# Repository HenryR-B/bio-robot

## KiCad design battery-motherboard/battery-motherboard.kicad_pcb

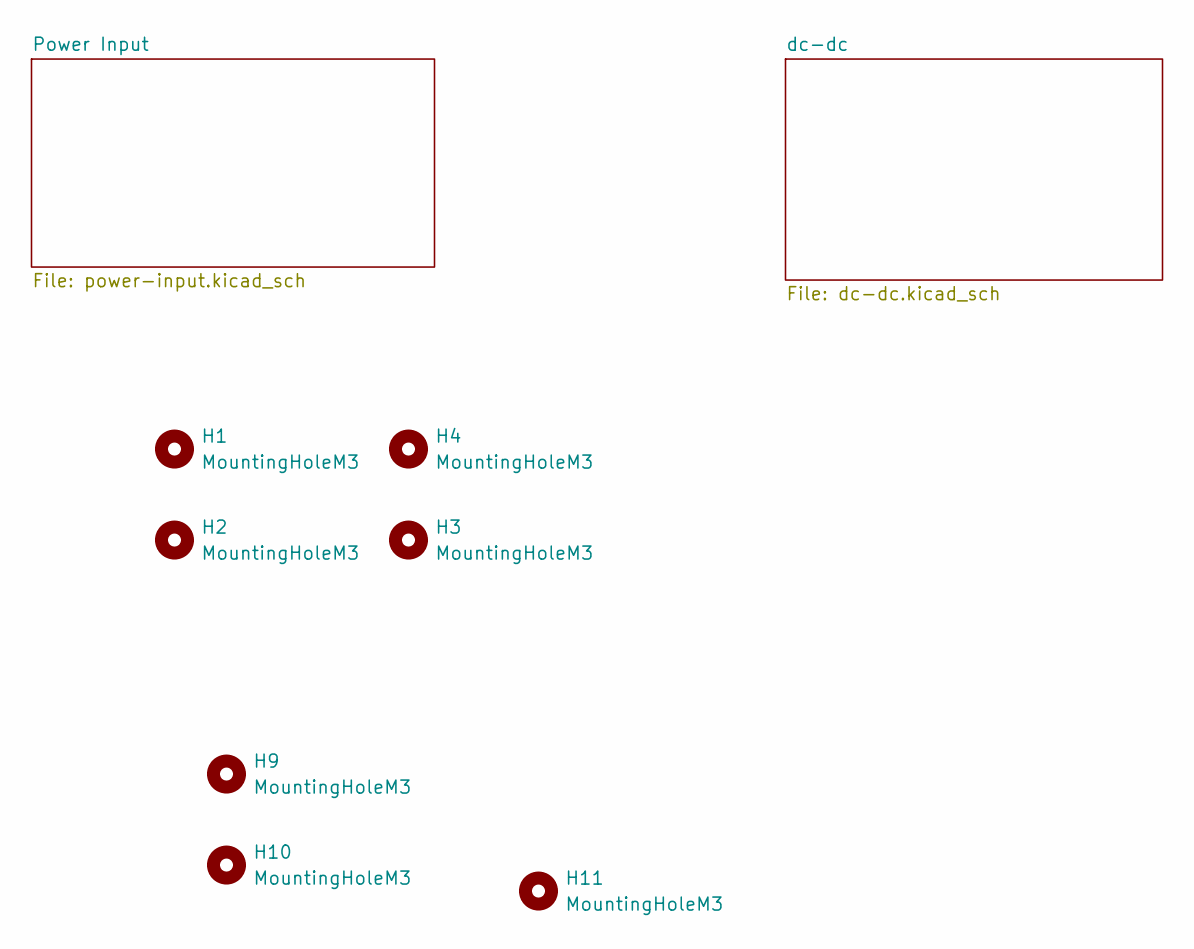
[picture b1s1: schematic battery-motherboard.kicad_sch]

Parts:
H1, H2, H3, H4, H9, H10, H11: MountingHoleM3; MountingHole_3.2mm_M3_DIN965_Pad

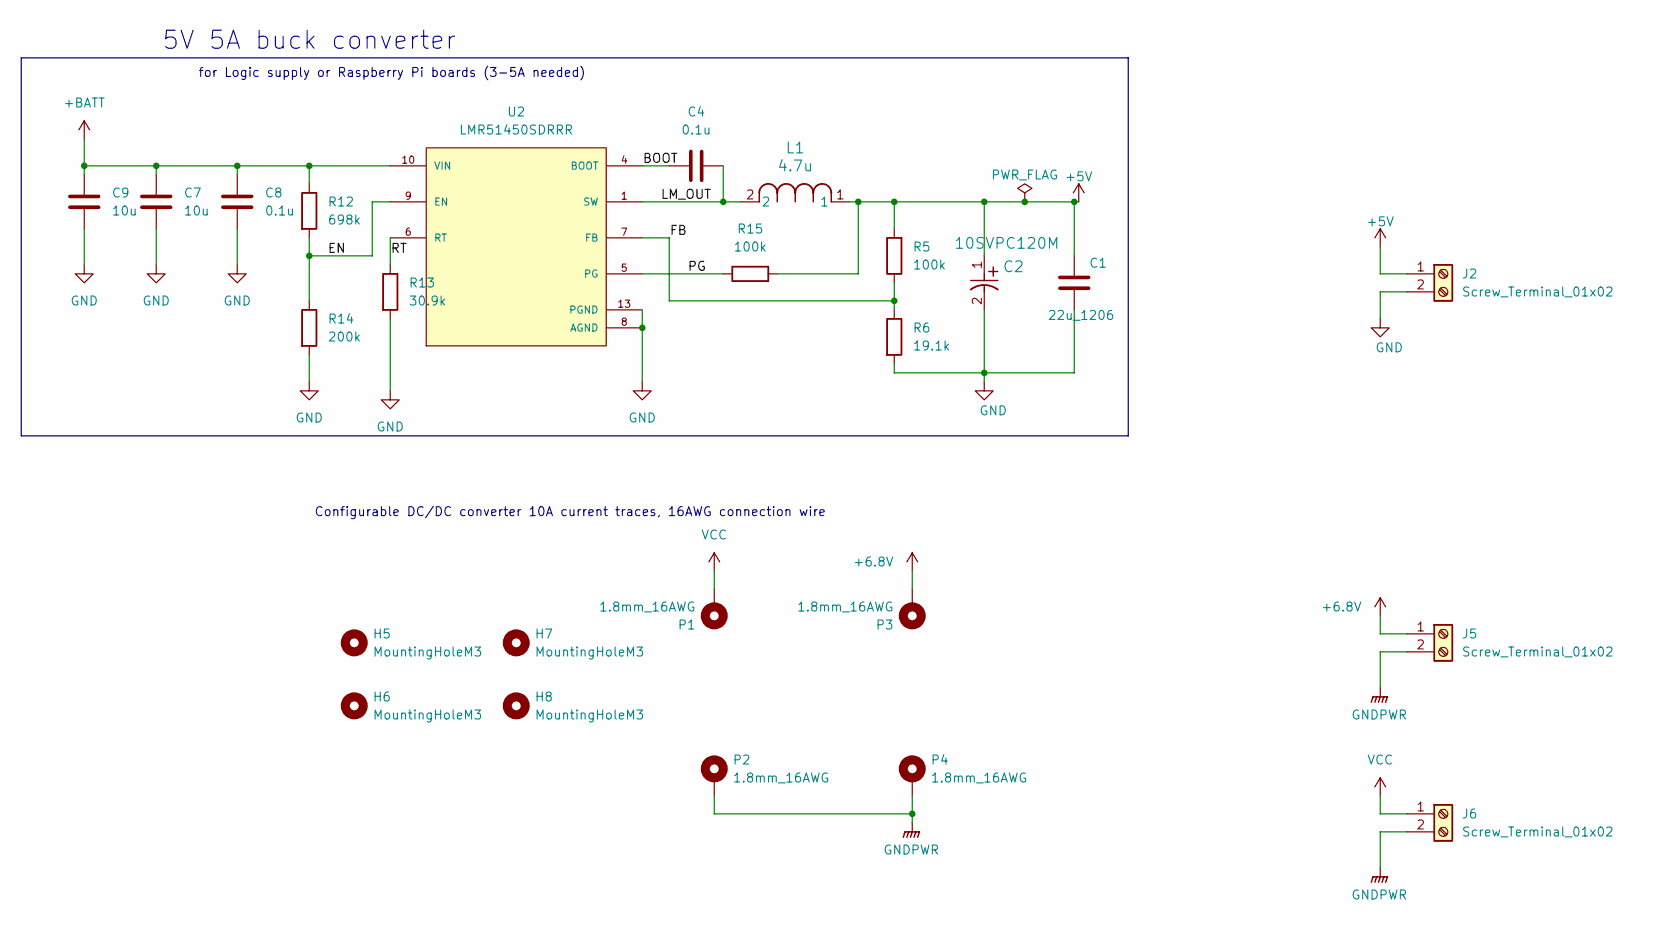
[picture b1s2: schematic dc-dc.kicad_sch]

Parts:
C1: 22u_1206; C_1206_3216Metric; MPN CL31A226KAHNNNE; JLC 0805
C2: 10SVPC120M; CAP_10SVPC120MV; LCSC C178336
C4, C8: 0.1u; C_0603_1608Metric; MPN CC0603KRX7R9BB104; JLC 0603
C7, C9: 10u; C_0805_2012Metric; MPN GRM21BR61H106KE43L; JLC 0805
H5, H6, H7, H8: MountingHoleM3; MountingHole_3.2mm_M3_DIN965_Pad
J2, J5, J6: Screw_Terminal_01x02; TerminalBlock_MaiXu_MX126-5.0-02P_1x02_P5.00mm
L1: 4.7u; IND_XAL6060-472MEC; MPN XAL6060-472MEB; LCSC C7421717
P1, P2, P3, P4: 1.8mm_16AWG; SolderPad_TH_16AWG_1.8mm
R5, R15: 100k; R_0603_1608Metric; MPN 0603WAF1003T5E; JLC 0603
R6: 19.1k; R_0603_1608Metric; MPN 0603WAF1912T5E; JLC 0603
R12: 698k; R_0603_1608Metric; MPN 0603WAF6983T5E; JLC 0603
R13: 30.9k; R_0603_1608Metric; MPN 0603WAF3092T5E; JLC 0603
R14: 200k; R_0603_1608Metric; MPN 0603WAF2003T5E; JLC 0603
U2: LMR51450SDRRR; CONV_LMR51450SDRRR; PARTREV December 2022

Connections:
+5V: C1.1, C2.1, J2.1, L1.1, R5.2, R15.2; also elsewhere on the board
+6.8V: J5.1, P3.1 (1_1); also elsewhere on the board
+BATT: C7.1, C8.2, C9.1, R12.1, U2.10 (VIN), U2.11 (VIN), U2.12 (VIN); also elsewhere on the board
/dc-dc/BOOT: C4.1, U2.4 (BOOT)
/dc-dc/EN: R12.2, R14.1, U2.9 (EN)
/dc-dc/FB: R5.1, R6.1, U2.7 (FB)
/dc-dc/LM_OUT: C4.2, L1.2, U2.1 (SW), U2.2 (SW), U2.3 (SW)
/dc-dc/PG: R15.1, U2.5 (PG)
/dc-dc/RT: R13.1, U2.6 (RT)
GND: C1.2, C2.2, C7.2, C8.1, C9.2, J2.2, R6.2, R13.2, R14.2, U2.8 (AGND), U2.13 (PGND); also elsewhere on the board
GNDPWR: J5.2, J6.2, P2.1 (1_1), P4.1 (1_1); also elsewhere on the board
VCC: J6.1, P1.1 (1_1); also elsewhere on the board

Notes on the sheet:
Configurable DC/DC converter 10A current traces, 16AWG connection wire
5V 5A buck converter
for Logic supply or Raspberry Pi boards (3-5A needed)

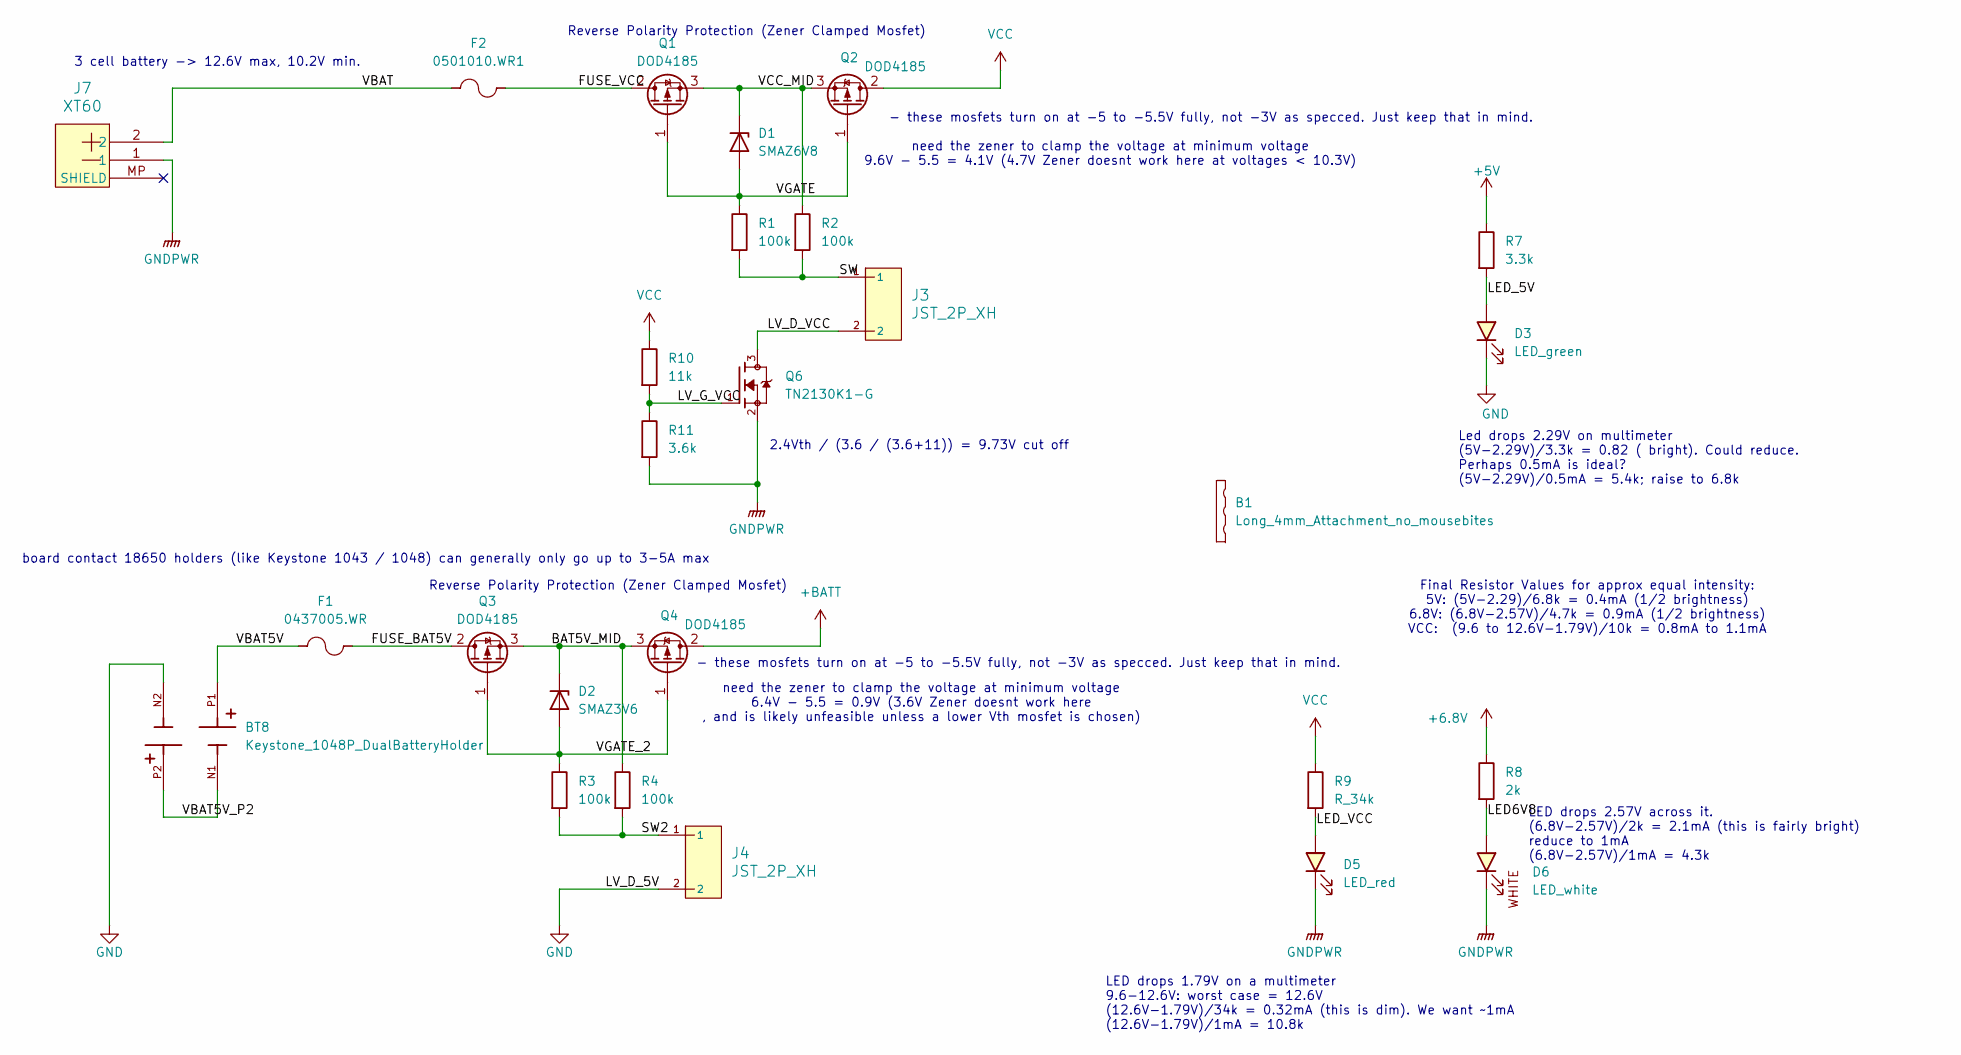
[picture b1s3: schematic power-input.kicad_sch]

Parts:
B1: Long_4mm_Attachment_no_mousebites; Long_4mm_attachment_no_mouse_bites
BT8: Keystone_1048P_DualBatteryHolder; BAT_1048P; PARTREV E; DigiKey_Part_Number 36-1042-ND
D1: SMAZ6V8; D_SMA; MPN SMAZ6V8; JLC DO-214AC(SMA)
D2: SMAZ3V6; D_SMA; MPN 1SMA4729A; LCSC C19077475
D3: LED_green; LED_0805_2012Metric; MPN KT-0805G; JLC 0805
D5: LED_red; LED_0805_2012Metric; MPN NCD0805R1; JLC 0805
D6: LED_white; LED_0603_1608Metric; MPN KT-0603W; JLC 0603
F1: 0437005.WR; Fuse_1206_3216Metric; MPN 0501010.WR1; JLC 1206
F2: 0501010.WR1; Fuse_1206_3216Metric; MPN 0501010.WR1; JLC 1206
J3, J4: JST_2P_XH; JST_B2B-XH-A_LF__SN_
J7: XT60; AMASS_XT60PW-M
Q1, Q2, Q3, Q4: DOD4185; DPAK-3_ONS; MPN DOD4185; LCSC C41430591
Q6: TN2130K1-G; SOT95P240X111-3N; MPN TN2130K1-G; JLC SOT-23-3
R1, R2, R3, R4: 100k; R_0603_1608Metric; MPN 0603WAF1003T5E; JLC 0603
R7: 3.3k; R_0603_1608Metric; MPN 0603WAF3301T5E; JLC 0603
R8: 2k; R_0603_1608Metric; MPN 0603WAF2001T5E; JLC 0603
R9: R_34k; R_0603_1608Metric; MPN 0603WAF3402T5E; JLC 0603
R10: 11k; R_0603_1608Metric; MPN 0603WAF1102T5E; JLC 0603
R11: 3.6k; R_0603_1608Metric; MPN 0603WAF3601T5E; JLC 0603

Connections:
+5V: R7.1; also elsewhere on the board
+6.8V: R8.1; also elsewhere on the board
+BATT: Q4.2 (D); also elsewhere on the board
/Power Input/BAT5V_MID: D2.1 (K), Q3.3 (S), Q4.3 (S), R4.1
/Power Input/FUSE_BAT5V: F1.2, Q3.2 (D)
/Power Input/FUSE_VCC: F2.2, Q1.2 (D)
/Power Input/LED6V8: D6.2 (A), R8.2
/Power Input/LED_5V: D3.2 (A), R7.2
/Power Input/LED_VCC: D5.2 (A), R9.2
/Power Input/LV_D_VCC: J3.2, Q6.3
/Power Input/LV_G_VCC: Q6.1, R10.2, R11.1
/Power Input/SW: J3.1, R1.2, R2.2
/Power Input/SW2: J4.1, R3.2, R4.2
/Power Input/VBAT: F2.1, J7.2
/Power Input/VBAT5V: BT8.P1, F1.1
/Power Input/VBAT5V_P2: BT8.N1, BT8.P2
/Power Input/VCC_MID: D1.1 (K), Q1.3 (S), Q2.3 (S), R2.1
/Power Input/VGATE: D1.2 (A), Q1.1 (G), Q2.1 (G), R1.1
/Power Input/VGATE_2: D2.2 (A), Q3.1 (G), Q4.1 (G), R3.1
GND: BT8.N2, D3.1 (K), J4.2; also elsewhere on the board
GNDPWR: D5.1 (K), D6.1 (K), J7.1, Q6.2, R11.2; also elsewhere on the board
VCC: Q2.2 (D), R9.1, R10.1; also elsewhere on the board

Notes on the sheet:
3 cell battery -> 12.6V max, 10.2V min.
Reverse Polarity Protection (Zener Clamped Mosfet)
2.4Vth / (3.6 / (3.6+11)) = 9.73V cut off
board contact 18650 holders (like Keystone 1043 / 1048) can generally only go up to 3-5A max
LED drops 2.57V across it. (6.8V-2.57V)/2k = 2.1mA (this is fairly bright) reduce to 1mA (6.8V-2.57V)/1mA = 4.3k
Final Resistor Values for approx equal intensity: 5V: (5V-2.29)/6.8k = 0.4mA (1/2 brightness) 6.8V: (6.8V-2.57V)/4.7k = 0.9mA (1/2 brightness) VCC: (9.6 to 12.6V-1.79V)/10k = 0.8mA to 1.1mA
need the zener to clamp the voltage at minimum voltage 9.6V - 5.5 = 4.1V (4.7V Zener doesnt work here at voltages < 10.3V)
- these mosfets turn on at -5 to -5.5V fully, not -3V as specced. Just keep that in mind.
need the zener to clamp the voltage at minimum voltage 6.4V - 5.5 = 0.9V (3.6V Zener doesnt work here , and is likely unfeasible unless a lower Vth mosfet is chosen)
LED drops 1.79V on a multimeter 9.6-12.6V: worst case = 12.6V (12.6V-1.79V)/34k = 0.32mA (this is dim). We want ~1mA (12.6V-1.79V)/1mA = 10.8k
Led drops 2.29V on multimeter (5V-2.29V)/3.3k = 0.82 ( bright). Could reduce. Perhaps 0.5mA is ideal? (5V-2.29V)/0.5mA = 5.4k; raise to 6.8k

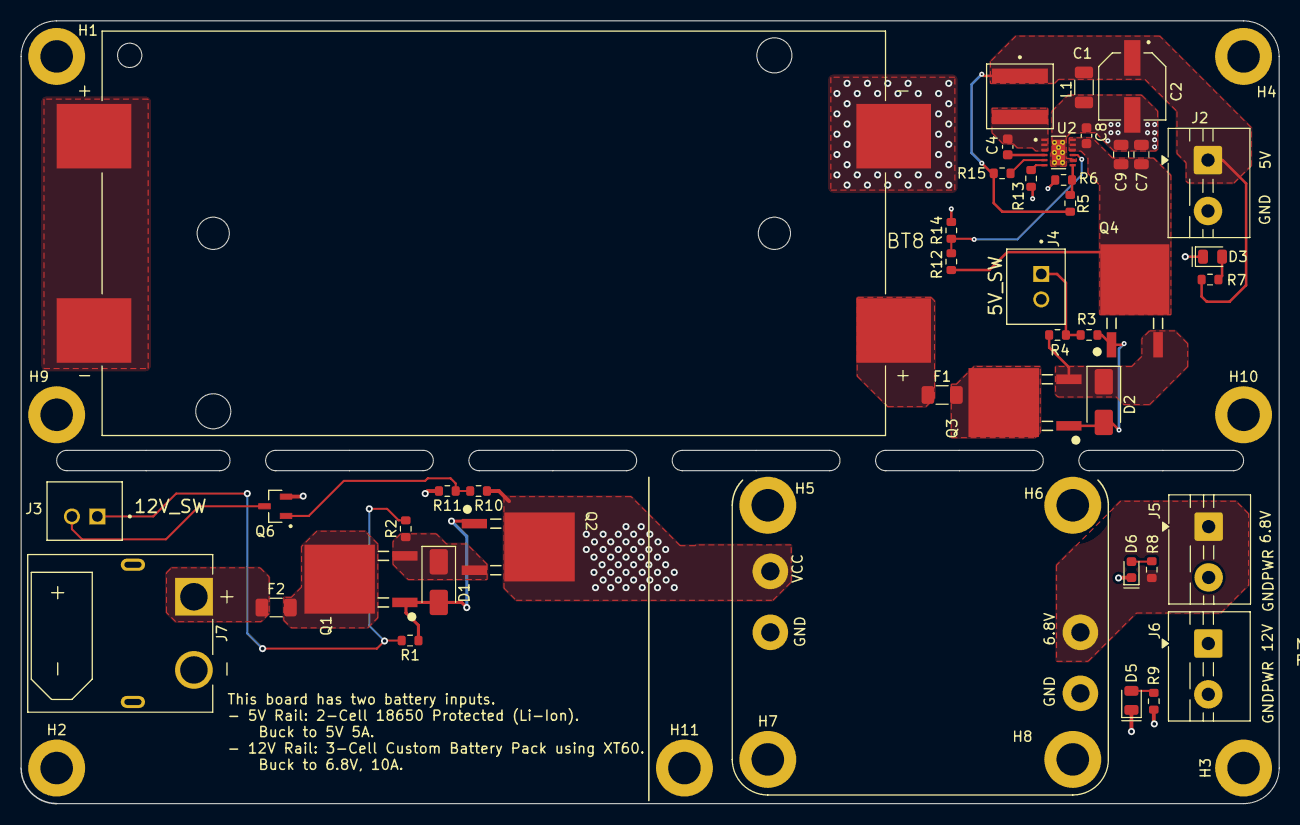
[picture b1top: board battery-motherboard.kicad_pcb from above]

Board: 4 copper layers, 123.7 x 77.0 mm, 58 parts (0 on the bottom side), 28 nets.

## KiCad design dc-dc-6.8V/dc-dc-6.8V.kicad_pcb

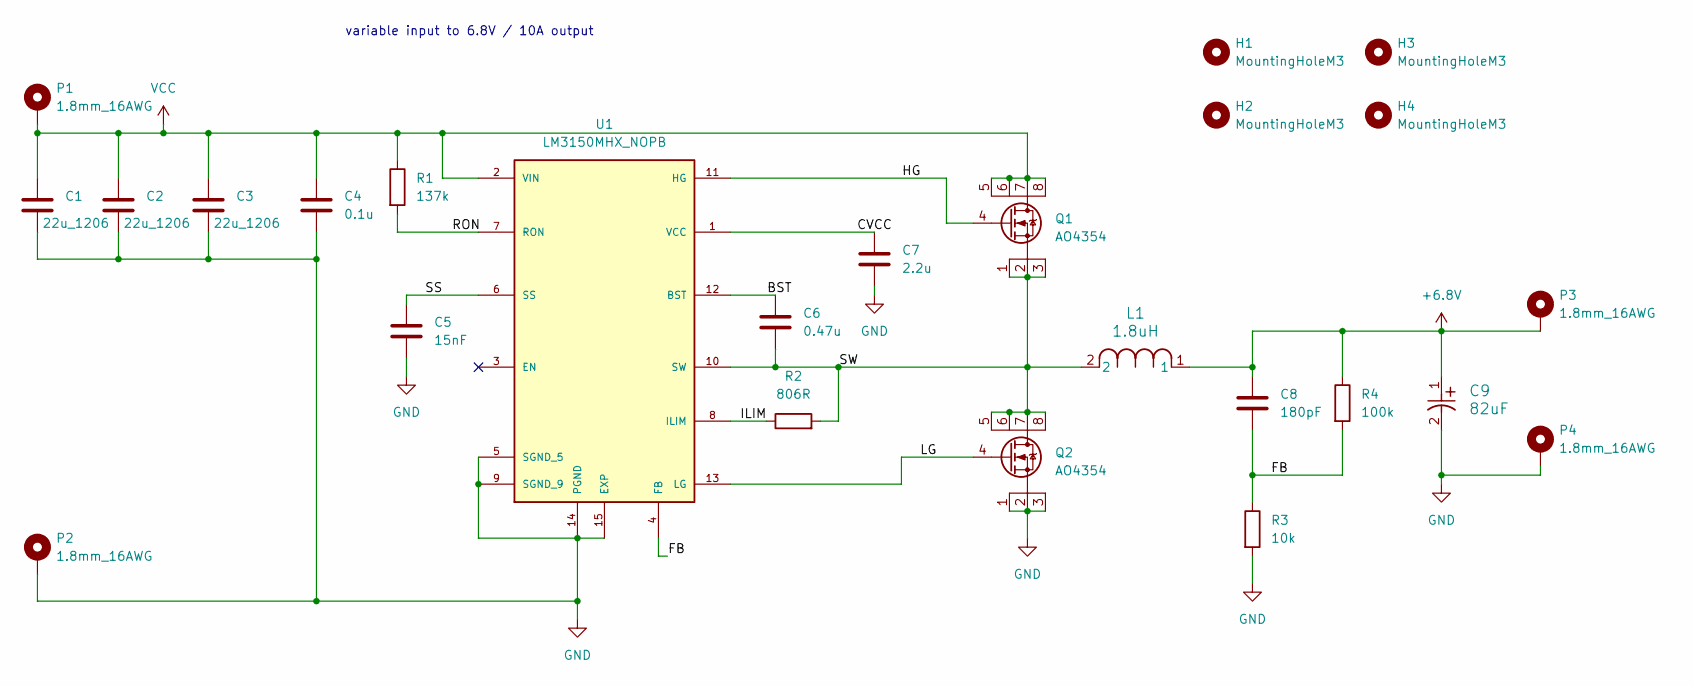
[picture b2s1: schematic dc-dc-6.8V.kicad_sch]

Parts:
C1, C2, C3: 22u_1206; C_1206_3216Metric; MPN CL31A226KAHNNNE; JLC 0805
C4: 0.1u; C_0603_1608Metric; MPN CC0603KRX7R9BB104; JLC 0603
C5: 15nF; C_0603_1608Metric; MPN 0603B153K500NT; JLC 0603
C6: 0.47u; C_0603_1608Metric; MPN CL10B474KA8NNNC; JLC 0603
C7: 2.2u; C_0603_1608Metric; MPN CL10A225KO8NNNC; JLC 0603
C8: 180pF; C_0603_1608Metric; MPN CL10C181JB8NNNC; JLC 0603
C9: 82uF; CAP_10SVPC120MV; MPN 10SVPC120MV; LCSC C178336
H1, H2, H3, H4: MountingHoleM3; MountingHole_3.2mm_M3_DIN965_Pad
L1: 1.8uH; IND_XAL7070_COC; MPN XAL7070-182MEC; LCSC C3911679
P1, P2, P3, P4: 1.8mm_16AWG; SolderPad_TH_16AWG_1.8mm
Q1, Q2: AO4354; SOIC-8_3.9x4.9mm_P1.27mm; MPN AO4354; LCSC C61955
R1: 137k; R_0603_1608Metric; MPN 0603WAF1373T5E; JLC 0603
R2: 806R; R_0603_1608Metric; MPN 0603WAF8060T5E; JLC 0603
R3: 10k; R_0603_1608Metric; MPN 0603WAF1002T5E; JLC 0603
R4: 100k; R_0603_1608Metric; MPN 0603WAF1003T5E; JLC 0603
U1: LM3150MHX_NOPB; SOP65P640X110-15N; PARTREV G

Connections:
+6.8V: C8.1, C9.1, L1.1, P3.1 (1_1), R4.1
/BST: C6.1, U1.12 (BST)
/CVCC: C7.1, U1.1 (VCC)
/FB: C8.2, R3.1, R4.2, U1.4 (FB)
/HG: Q1.4 (G), U1.11 (HG)
/ILIM: R2.1, U1.8 (ILIM)
/LG: Q2.4 (G), U1.13 (LG)
/RON: R1.2, U1.7 (RON)
/SS: C5.1, U1.6 (SS)
/SW: C6.2, L1.2, Q1.1 (S), Q1.2 (S), Q1.3 (S), Q2.5 (D), Q2.6 (D), Q2.7 (D), Q2.8 (D), R2.2, U1.10 (SW)
GND: C1.2, C2.2, C3.2, C4.2, C5.2, C7.2, C9.2, P2.1 (1_1), P4.1 (1_1), Q2.1 (S), Q2.2 (S), Q2.3 (S), R3.2, U1.5 (SGND_5), U1.9 (SGND_9), U1.14 (PGND), U1.15 (EXP)
VCC: C1.1, C2.1, C3.1, C4.1, P1.1 (1_1), Q1.5 (D), Q1.6 (D), Q1.7 (D), Q1.8 (D), R1.1, U1.2 (VIN)

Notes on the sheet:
variable input to 6.8V / 10A output

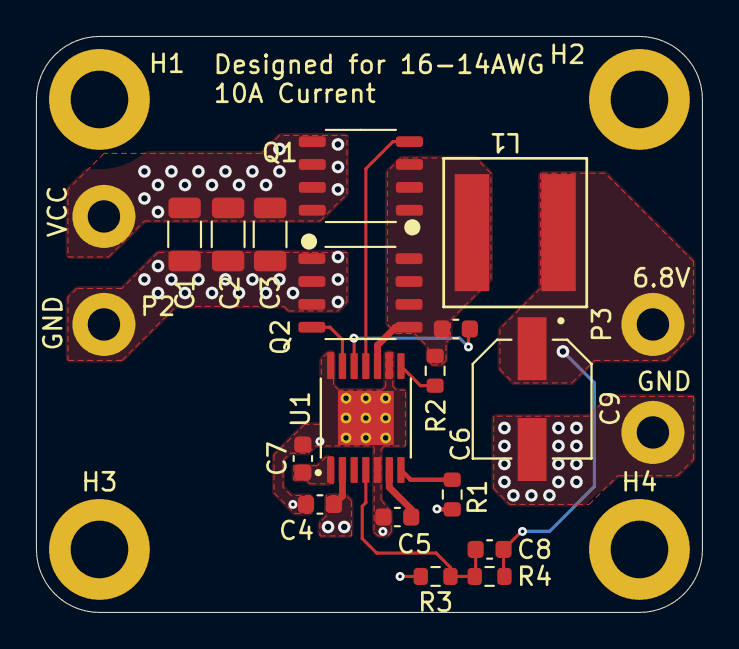
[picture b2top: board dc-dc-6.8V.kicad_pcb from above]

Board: 4 copper layers, 37.0 x 32.0 mm, 25 parts (0 on the bottom side), 12 nets.

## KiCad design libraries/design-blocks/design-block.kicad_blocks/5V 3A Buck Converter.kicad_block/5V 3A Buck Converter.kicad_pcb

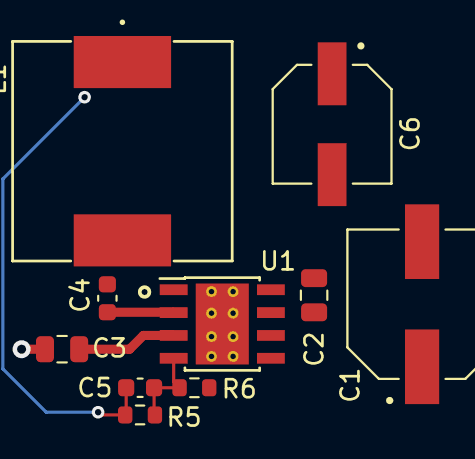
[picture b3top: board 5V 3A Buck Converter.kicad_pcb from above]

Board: 4 copper layers, 10 parts (0 on the bottom side), 7 nets.

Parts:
C1: 25SVPF100M; CAP_25SVPF100M
C2: 10u; C_0805_2012Metric
C3: 2.2u; C_0805_2012Metric
C4: 0.1u; C_0603_1608Metric
C5: 30p; C_0603_1608Metric
C6: 16SVPF180M; CAP_16SVPF180M
L1: 27uH; IND_CDRH127_LDNP-470MC_SUM
R5: 88.7k; R_0603_1608Metric
R6: 22.1k; R_0603_1608Metric
U1: LMR23630AFDDAR; TI_SO-PowerPAD-8_ThermalVias

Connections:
+5V: C5.1, C6.1, L1.1, R5.1
+BATT: C1.1, C2.1, U1.5 (EN/SYNC), U1.7 (VIN)
/dc-dc/BOOT: C4.1, U1.2 (BOOT)
/dc-dc/FB: C5.2, R5.2, R6.1, U1.4 (FB)
/dc-dc/LM_OUT: C4.2, L1.2, U1.1 (SW)
/dc-dc/U1_VCC: C3.1, U1.3 (VCC)
GND: C1.2, C2.2, C3.2, C6.2, R6.2, U1.6 (AGND), U1.8 (PGND), U1.9 (PAD)

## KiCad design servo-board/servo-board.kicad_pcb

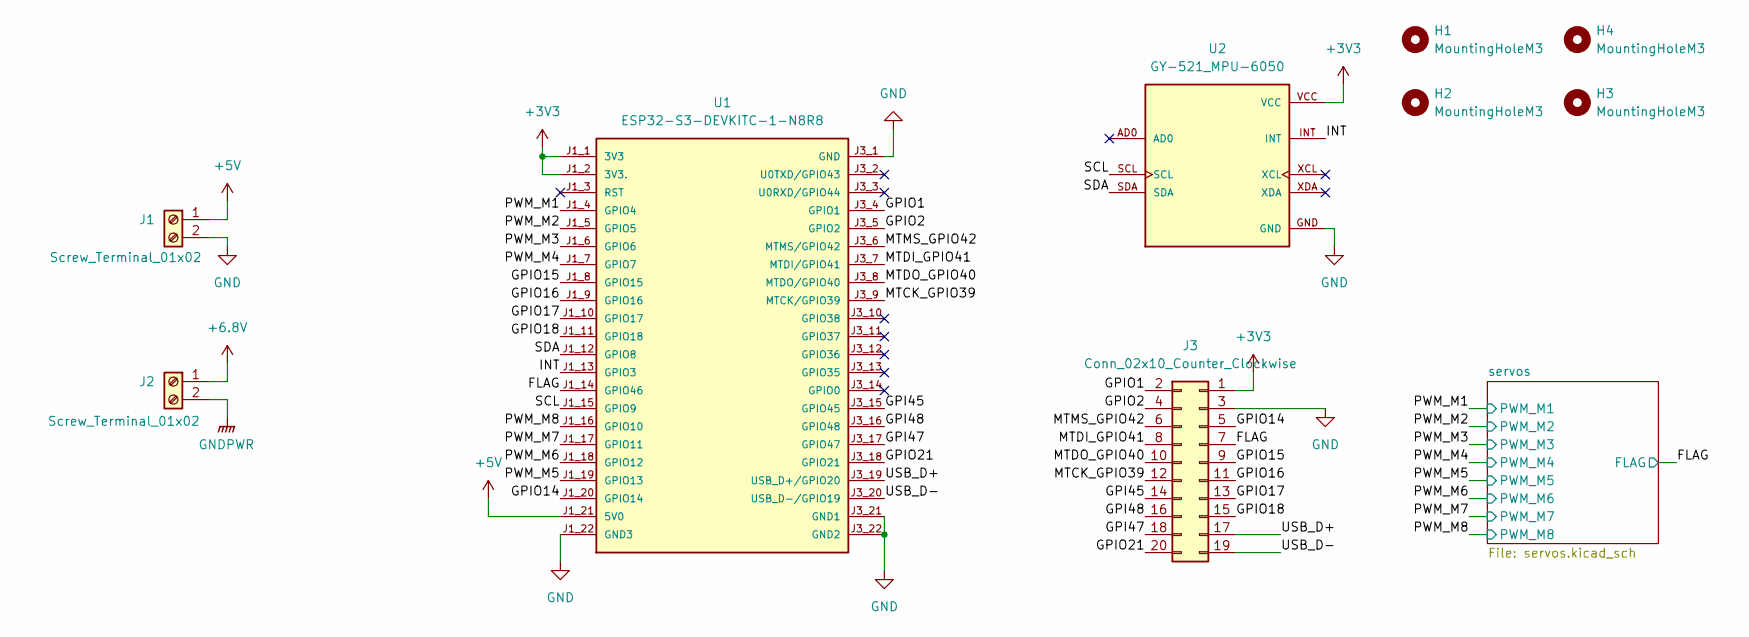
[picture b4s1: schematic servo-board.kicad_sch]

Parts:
H1, H2, H3, H4: MountingHoleM3; MountingHole_3.2mm_M3_DIN965_Pad
J1, J2: Screw_Terminal_01x02; TerminalBlock_MaiXu_MX126-5.0-02P_1x02_P5.00mm
J3: Conn_02x10_Counter_Clockwise; PinSocket_2x10_P2.54mm_Vertical
U1: ESP32-S3-DEVKITC-1-N8R8
U2: GY-521_MPU-6050; MODULE_OC09600; PARTREV NA

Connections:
+3V3: J3.1, U1.J1_1 (3V3), U1.J1_2 (3V3.), U2.VCC; also elsewhere on the board
+5V: J1.1, U1.J1_21 (5V0)
+6.8V: J2.1; also elsewhere on the board
/FLAG: J3.7, U1.J1_14 (GPIO46); also elsewhere on the board
/GPI45: J3.14, U1.J3_15 (GPIO45)
/GPI47: J3.18, U1.J3_17 (GPIO47)
/GPI48: J3.16, U1.J3_16 (GPIO48)
/GPIO1: J3.2, U1.J3_4 (GPIO1)
/GPIO2: J3.4, U1.J3_5 (GPIO2)
/GPIO14: J3.5, U1.J1_20 (GPIO14)
/GPIO15: J3.9, U1.J1_8 (GPIO15)
/GPIO16: J3.11, U1.J1_9 (GPIO16)
/GPIO17: J3.13, U1.J1_10 (GPIO17)
/GPIO18: J3.15, U1.J1_11 (GPIO18)
/GPIO21: J3.20, U1.J3_18 (GPIO21)
/INT: U1.J1_13 (GPIO3), U2.INT
/MTCK_GPIO39: J3.12, U1.J3_9 (MTCK/GPIO39)
/MTDI_GPIO41: J3.8, U1.J3_7 (MTDI/GPIO41)
/MTDO_GPIO40: J3.10, U1.J3_8 (MTDO/GPIO40)
/MTMS_GPIO42: J3.6, U1.J3_6 (MTMS/GPIO42)
/PWM_M1: U1.J1_4 (GPIO4); also elsewhere on the board
/PWM_M2: U1.J1_5 (GPIO5); also elsewhere on the board
/PWM_M3: U1.J1_6 (GPIO6); also elsewhere on the board
/PWM_M4: U1.J1_7 (GPIO7); also elsewhere on the board
/PWM_M5: U1.J1_19 (GPIO13); also elsewhere on the board
/PWM_M6: U1.J1_18 (GPIO12); also elsewhere on the board
/PWM_M7: U1.J1_17 (GPIO11); also elsewhere on the board
/PWM_M8: U1.J1_16 (GPIO10); also elsewhere on the board
/SCL: U1.J1_15 (GPIO9), U2.SCL
/SDA: U1.J1_12 (GPIO8), U2.SDA
/USB_D+: J3.17, U1.J3_19 (USB_D+/GPIO20)
/USB_D-: J3.19, U1.J3_20 (USB_D-/GPIO19)
GND: J1.2, J3.3, U1.J1_22 (GND3), U1.J3_1 (GND), U1.J3_21 (GND1), U1.J3_22 (GND2), U2.GND; also elsewhere on the board
GNDPWR: J2.2; also elsewhere on the board

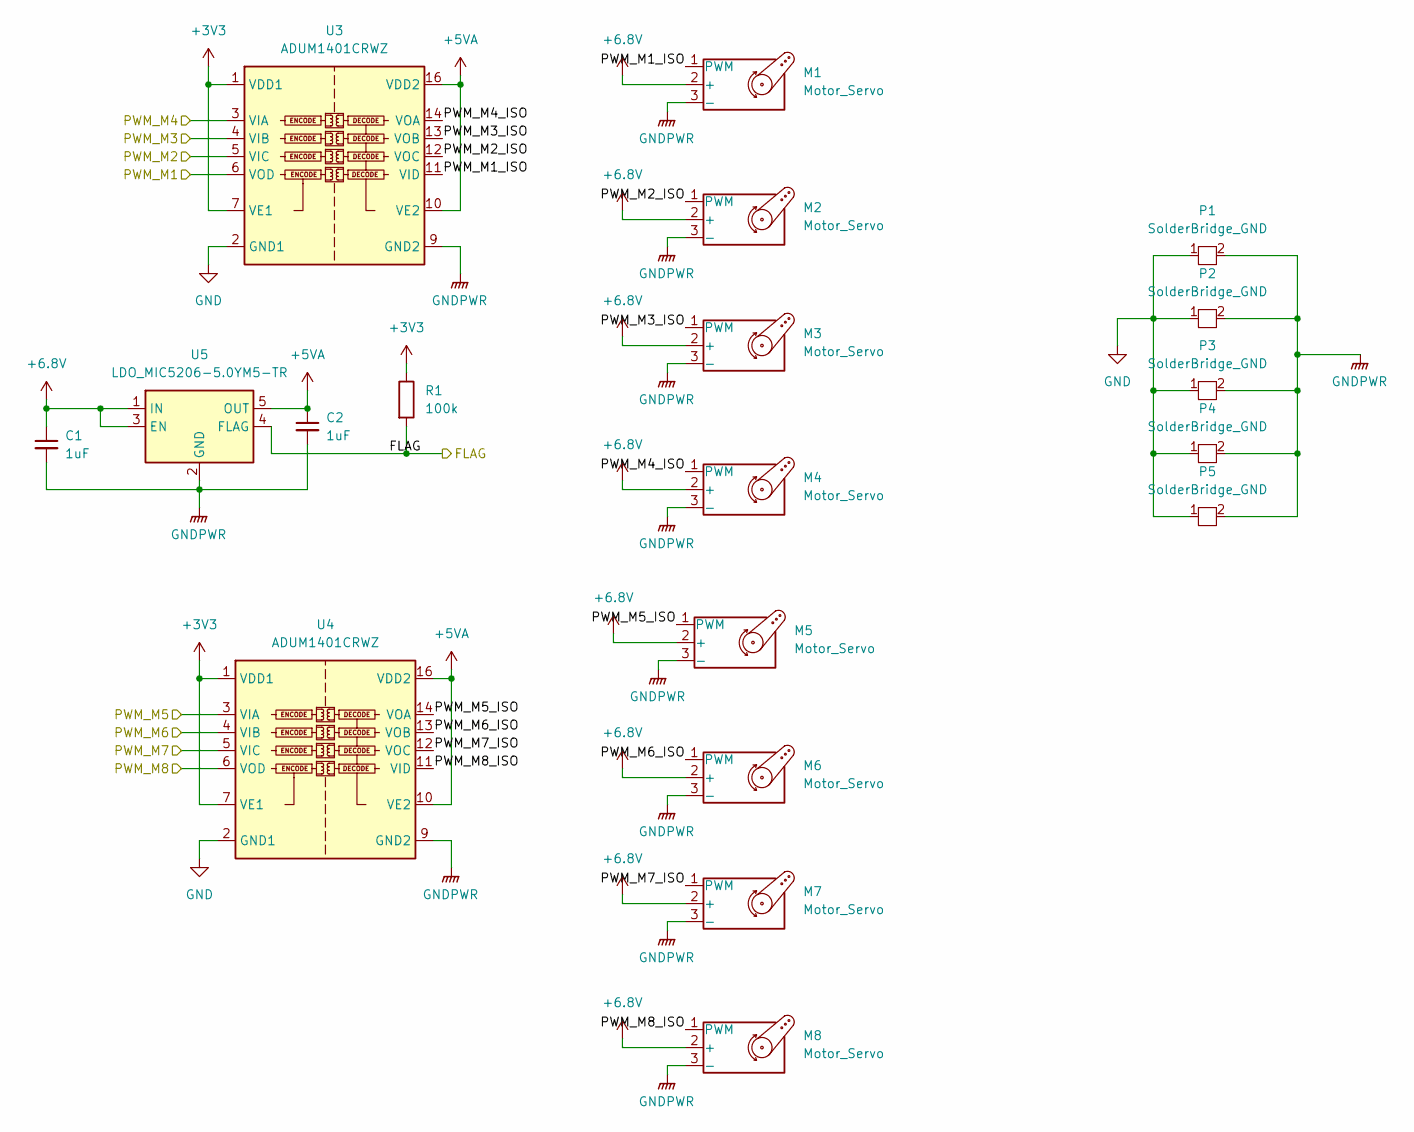
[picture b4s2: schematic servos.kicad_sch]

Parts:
C1, C2: 1uF; C_0603_1608Metric; MPN CL10A105KB8NNNC; LCSC C15849
M1, M2, M3, M4, M5, M6, M7, M8: Motor_Servo; PinHeader_1x03_P2.54mm_Vertical
P1, P2, P3, P4, P5: SolderBridge_GND
R1: 100k; R_0603_1608Metric; MPN 0603WAF1003T5E; JLC 0603
U3, U4: ADUM1401CRWZ; SOIC-16W_7.5x10.3mm_P1.27mm
U5: LDO_MIC5206-5.0YM5-TR; SOT-23-5

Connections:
+3V3: R1.1, U3.1 (VDD1), U3.7 (VE1), U4.1 (VDD1), U4.7 (VE1); also elsewhere on the board
+5VA: C2.1, U3.10 (VE2), U3.16 (VDD2), U4.10 (VE2), U4.16 (VDD2), U5.5 (OUT)
+6.8V: C1.1, M1.2 (+), M2.2 (+), M3.2 (+), M4.2 (+), M5.2 (+), M6.2 (+), M7.2 (+), M8.2 (+), U5.1 (IN), U5.3 (EN); also elsewhere on the board
/FLAG: R1.2, U5.4 (FLAG); also elsewhere on the board
/PWM_M1: U3.6 (VOD); also elsewhere on the board
/PWM_M2: U3.5 (VIC); also elsewhere on the board
/PWM_M3: U3.4 (VIB); also elsewhere on the board
/PWM_M4: U3.3 (VIA); also elsewhere on the board
/PWM_M5: U4.3 (VIA); also elsewhere on the board
/PWM_M6: U4.4 (VIB); also elsewhere on the board
/PWM_M7: U4.5 (VIC); also elsewhere on the board
/PWM_M8: U4.6 (VOD); also elsewhere on the board
/servos/PWM_M1_ISO: M1.1 (PWM), U3.11 (VID)
/servos/PWM_M2_ISO: M2.1 (PWM), U3.12 (VOC)
/servos/PWM_M3_ISO: M3.1 (PWM), U3.13 (VOB)
/servos/PWM_M4_ISO: M4.1 (PWM), U3.14 (VOA)
/servos/PWM_M5_ISO: M5.1 (PWM), U4.14 (VOA)
/servos/PWM_M6_ISO: M6.1 (PWM), U4.13 (VOB)
/servos/PWM_M7_ISO: M7.1 (PWM), U4.12 (VOC)
/servos/PWM_M8_ISO: M8.1 (PWM), U4.11 (VID)
GND: P1.1, P2.1, P3.1, P4.1, P5.1, U3.2 (GND1), U3.8 (GND1), U4.2 (GND1), U4.8 (GND1); also elsewhere on the board
GNDPWR: C1.2, C2.2, M1.3 (-), M2.3 (-), M3.3 (-), M4.3 (-), M5.3 (-), M6.3 (-), M7.3 (-), M8.3 (-), P1.2, P2.2, P3.2, P4.2, P5.2, U3.9 (GND2), U3.15 (GND2), U4.9 (GND2), U4.15 (GND2), U5.2 (GND); also elsewhere on the board

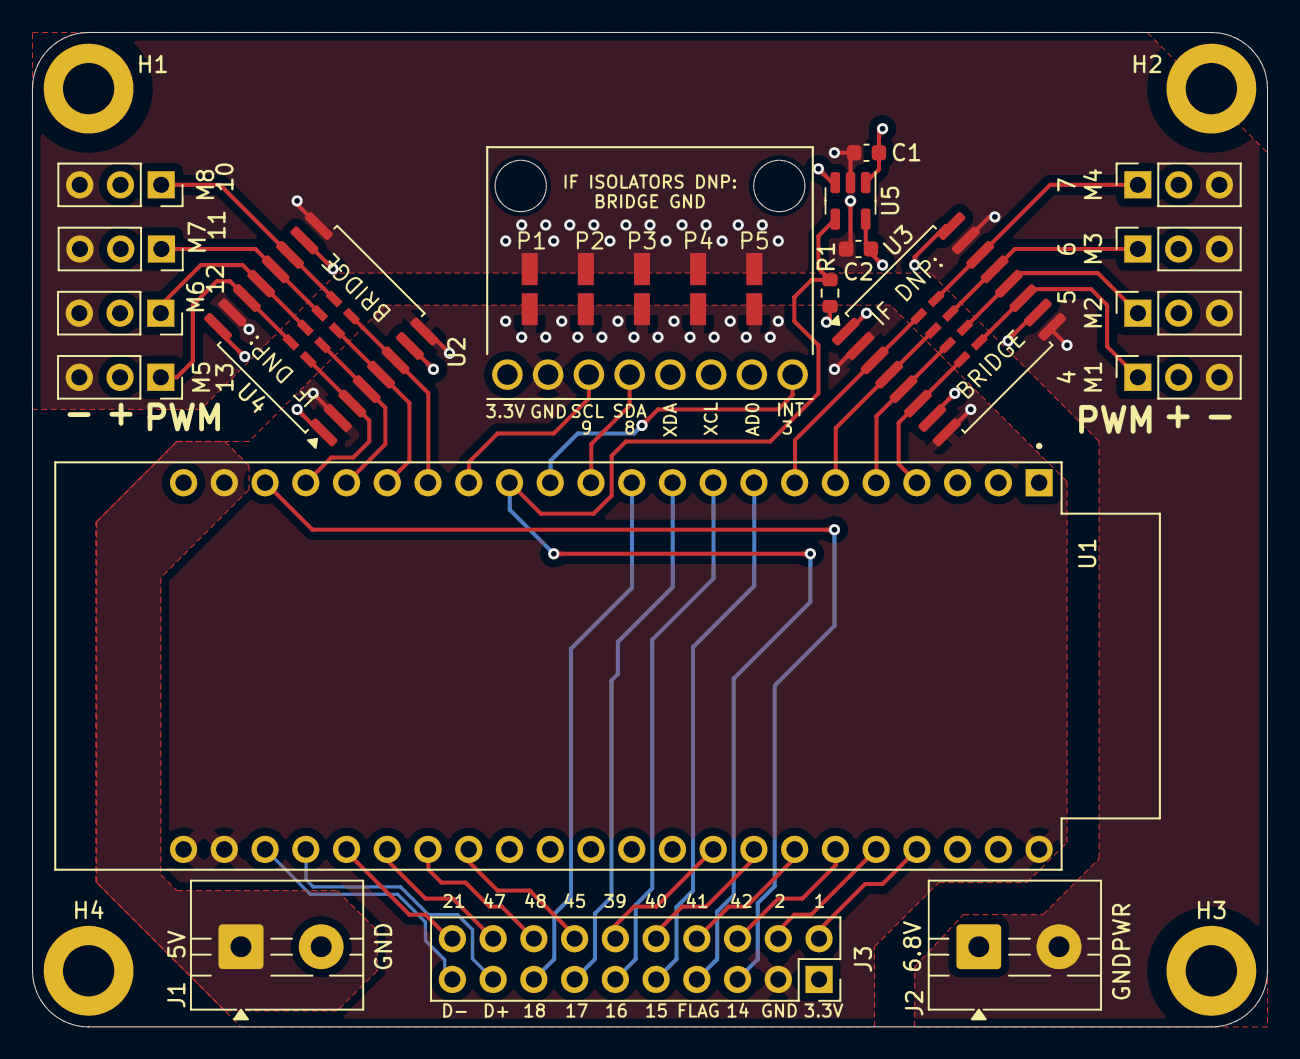
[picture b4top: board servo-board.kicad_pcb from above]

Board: 4 copper layers, 77.0 x 62.0 mm, 28 parts (0 on the bottom side), 43 nets.

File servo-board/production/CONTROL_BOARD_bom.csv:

Designator,Footprint,Quantity,Value,LCSC Part #
"C1, C2",0603,2,1uF,C15849
"J1, J2",TerminalBlock_MaiXu_MX126-5.0-02P_1x02_P5.00mm,2,Screw_Terminal_01x02,
J3,PinSocket_2x10_P2.54mm_Vertical,1,Conn_02x10_Counter_Clockwise,
"M1, M2, M3, M4, M5, M6, M7, M8",PinHeader_1x03_P2.54mm_Vertical,8,Motor_Servo,
"P1, P2, P3, P4, P5",SolderBridge_GND,5,SolderBridge_GND,
R1,0603,1,100k,C25803
U1,ESP32-S3-DEVKITC-1-N8R8,1,ESP32-S3-DEVKITC-1-N8R8,
U2,MODULE_OC09600,1,GY-521_MPU-6050,
"U3, U4",SOIC-16W_7.5x10.3mm_P1.27mm,2,ADUM1401CRWZ,
U5,SOT-23-5,1,LDO_MIC5206-5.0YM5-TR,

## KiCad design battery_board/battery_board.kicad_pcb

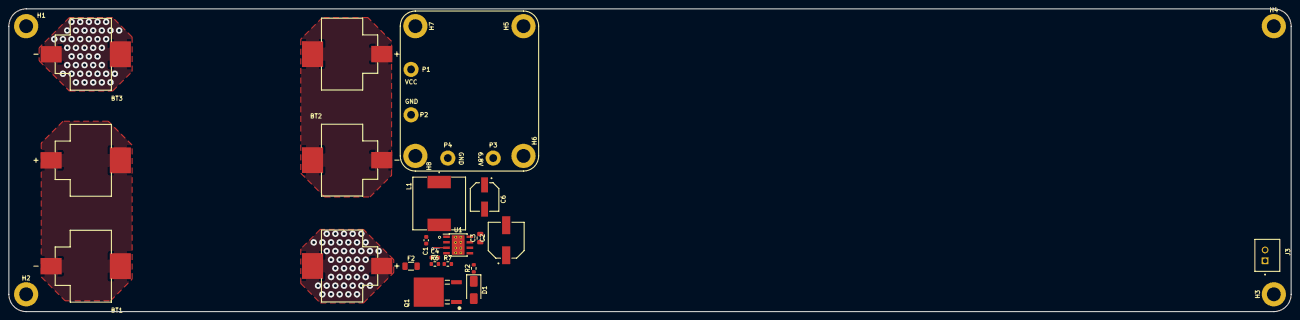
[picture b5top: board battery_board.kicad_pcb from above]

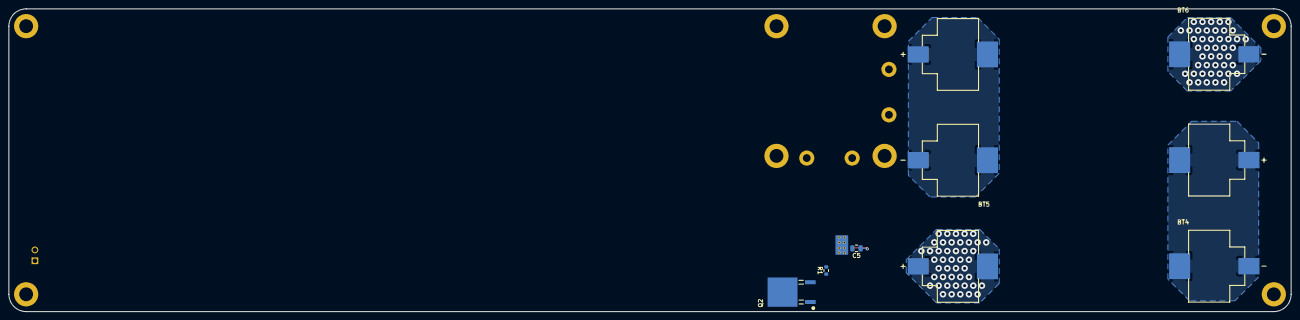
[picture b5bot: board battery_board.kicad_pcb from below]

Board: 4 copper layers, 296.5 x 70.0 mm, 35 parts (6 on the bottom side), 16 nets.

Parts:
BT1, BT2, BT3, BT4, BT5, BT6: Keystone_254_BatteryClip_Holder; BAT_254_18650_Holder
C1: 0.1u; C_0603_1608Metric
C2: 25SVPF100M; CAP_25SVPF100M
C3: 10u; C_0805_2012Metric
C4: 30p; C_0603_1608Metric
C5: 2.2u; C_0805_2012Metric
C6: 16SVPF180M; CAP_16SVPF180M
D1: SMAZ6V8; D_SMA
F2: 0501010.WR1; Fuse_1206_3216Metric
H1, H2, H3, H4, H5, H6, H7, H8: MountingHoleM3; MountingHole_3.2mm_M3_DIN965_Pad
J3: JST_2P_XH; JST_B2B-XH-A_LF__SN_
L1: 27uH; IND_CDRH127_LDNP-470MC_SUM
P1, P2, P3, P4: 1.8mm_16AWG; SolderPad_TH_16AWG_1.8mm
Q1, Q2: DOD4185; DPAK-3_ONS
R1, R2: 100k; R_0603_1608Metric
R6: 88.7k; R_0603_1608Metric
R7: 22.1k; R_0603_1608Metric
U1: LMR23630AFDDAR; TI_SO-PowerPAD-8_ThermalVias

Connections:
+5V: C4.1, C6.1, L1.1, R6.1
/Power Input/FUSE_VCC: F2.2, Q1.2 (D)
/Power Input/P2+: BT1.P-, BT2.P+
/Power Input/P3+: BT2.P-, BT3.P+
/Power Input/P5+: BT4.P-, BT5.P+
/Power Input/P6+: BT5.P-, BT6.P+
/Power Input/SW: J3.1, R1.2, R2.2
/Power Input/VBAT: BT1.P+, BT4.P+, F2.1
/Power Input/VCC_MID: D1.1 (K), Q1.3 (S), Q2.3 (S), R2.1
/Power Input/VGATE: D1.2 (A), Q1.1 (G), Q2.1 (G), R1.1
/dc-dc/BOOT: C1.1, U1.2 (BOOT)
/dc-dc/FB: C4.2, R6.2, R7.1, U1.4 (FB)
/dc-dc/LM_OUT: C1.2, L1.2, U1.1 (SW)
/dc-dc/U1_VCC: C5.1, U1.3 (VCC)
GND: BT3.P-, BT6.P-, C2.2, C3.2, C5.2, C6.2, J3.2, P2.1, P4.1, R7.2, U1.6 (AGND), U1.8 (PGND), U1.9 (PAD)
VCC: C2.1, C3.1, P1.1, Q2.2 (D), U1.5 (EN/SYNC), U1.7 (VIN)

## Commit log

2026-03-02 elec
2026-03-03 boards
2026-03-03 symlib
2026-03-03 proof of concept
2026-03-04 split into two boards for dc/dc converter
2026-03-12 board
2026-03-13 board done
2026-03-13 control board ordered
2026-03-24 board files
2026-03-25 update to silkscreen
2026-03-25 adding leds
    - need to add UVLO
2026-03-26 5V 5A version
2026-03-27 ordered
2026-04-10 zener notes
2026-04-10 control board name change
2026-04-26 naming
